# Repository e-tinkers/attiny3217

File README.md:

## E-Tinkers ATtiny3217 Arduino-Compatible Development Board

This is the hardware design repository for a tiny (34.6mm * 19.3mm) Arduino-compatible Development Board based on ATtiny3271.

ATtiny3217 is a modern AVR microcontroller chip from Microchip that could potentially replace ATmega328p that is widely used in official Arduino boards. Traditionally the classic ATtiny family has low flash and SRAM memory size as well as low pin count, this has changed since the release of tinyAVR 0-series and 1-series MCUs in 2018. The following table shows ATtiny3217 offers almost all the features of an ATmega328p and more...

### Differences between ATmega328p and ATtiny3217
<table>
    <tr>
        <th></th>
        <th>ATmega328p</th>
        <th>ATtiny3217</th>
    </tr>
    <tr>
        <td>Flash Memory</td>
        <td>32K Bytes</td>
        <td>32K Bytes</td>
    </tr>
    <tr>
        <td>SRAM</td>
        <td>2K Bytes</td>
        <td>2K Bytes</td>
    </tr>
    <tr>
        <td>EEPROM</td>
        <td>1K Bytes</td>
        <td>256 Bytes</td>
    </tr>
    <tr>
        <td>UART</td>
        <td>1</td>
        <td>1</td>
    </tr>
    <tr>
        <td>SPI</td>
        <td>1</td>
        <td>1</td>
    </tr>
    <tr>
        <td>I2C</td>
        <td>1</td>
        <td>1</td>
    </tr>
    <tr>
        <td>ADC Channel</td>
        <td>8 x 10-bit</td>
        <td>12 x 10-bit</td>
    </tr>
    <tr>
        <td>PWM Channel</td>
        <td>6</td>
        <td>8</td>
    </tr>
    <tr>
        <td>IO</td>
        <td>23</td>
        <td>22</td>
    </tr>
    <tr>
        <td rowspan="3">Timer</td>
        <td rowspan="3">
        2 x 8-bit<br>
        1 x 16-bit
        </td>
        <td rowspan="3">
        1 x 16-bit(TCA)<br>
        2 x 16-bit (TCB)<br>
        1 x 12-bit (TCD)
        </td>
    </tr>
</table>

There are several notible features that are not available in ATmega328p, such as:
<ul>
<li>Three 8-bit DACs with one external channel</li>
<li>Configurable Custom Logic/Lookup Table</li>
<li>16-bit Real-time Counter</li>
<li>6 Event System Channels</li>
<li>Periperral Touch Controller</li>
<li>5 Configurable Internal Voltage References (versus ATmega328p's 1 at VCC level)</li>
</ul>

Read my [blog](https://www.e-tinkers.com/2020/07/arduino-compatible-development-board-with-attiny3217) for more details on how to use it as an Arduino.

## E-Tinkers ATtiny3217 Development Board Pinout

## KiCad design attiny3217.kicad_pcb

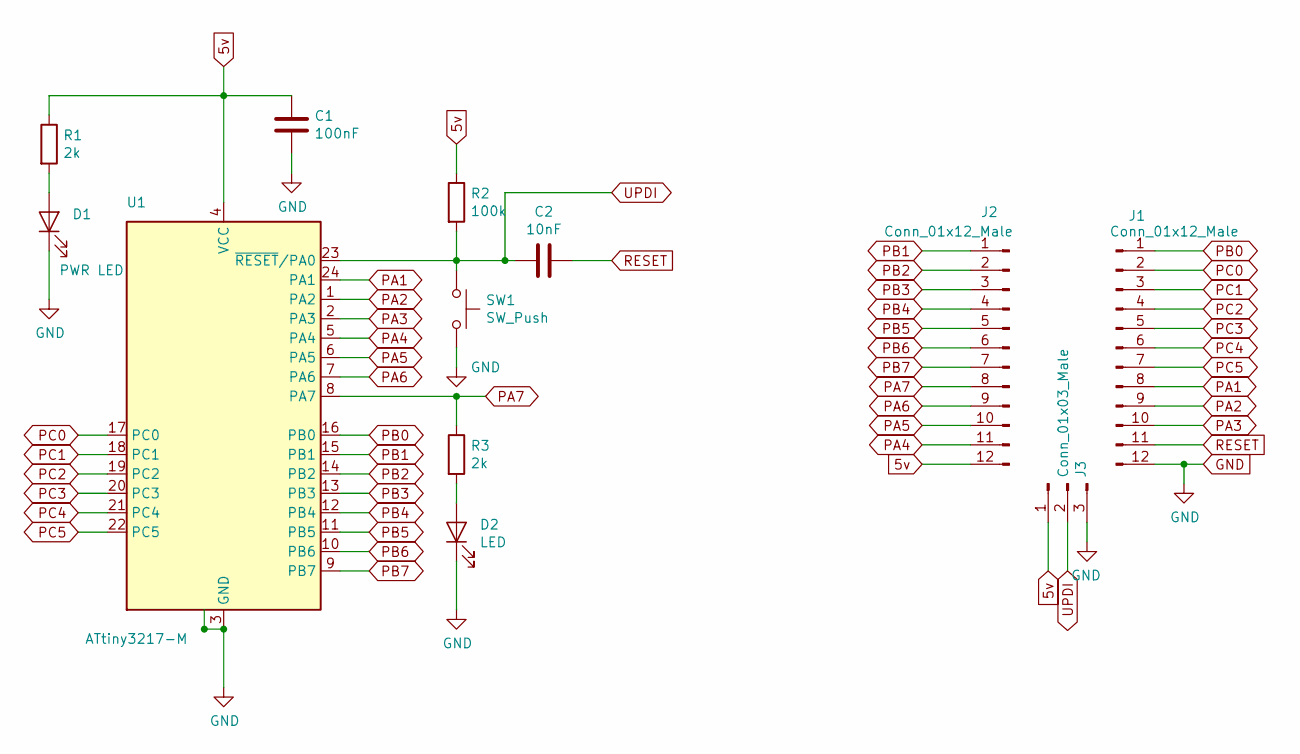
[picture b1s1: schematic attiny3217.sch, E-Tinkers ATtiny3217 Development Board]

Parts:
C1: 100nF; C_0805_2012Metric
C2: 10nF; C_0805_2012Metric
D1: PWR LED; LED_0805_2012Metric
D2: LED; LED_0805_2012Metric
J1, J2: Conn_01x12_Male; PinHeader_1x12_P2.54mm_Vertical
J3: Conn_01x03_Male; PinHeader_1x03_P2.54mm_Horizontal
R1, R3: 2k; R_0805_2012Metric
R2: 100k; R_0805_2012Metric
SW1: SW_Push; SW_SPST_CK_RS282G05A3
U1: ATtiny3217-M; QFN-24-1EP_4x4mm_P0.5mm_EP2.6x2.6mm

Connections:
5v: C1.1, J2.12, J3.1, R1.1, R2.1, U1.4 (VCC)
GND: C1.2, D1.1 (K), D2.1 (K), J1.12, J3.3, SW1.2, U1.3 (GND), U1.25 (GND)
unnamed: D1.2 (A), R1.2
unnamed: D2.2 (A), R3.2
PA1: J1.8, U1.24 (PA1)
PA2: J1.9, U1.1 (PA2)
PA3: J1.10, U1.2 (PA3)
PA4: J2.11, U1.5 (PA4)
PA5: J2.10, U1.6 (PA5)
PA6: J2.9, U1.7 (PA6)
PA7: J2.8, R3.1, U1.8 (PA7)
PB0: J1.1, U1.16 (PB0)
PB1: J2.1, U1.15 (PB1)
PB2: J2.2, U1.14 (PB2)
PB3: J2.3, U1.13 (PB3)
PB4: J2.4, U1.12 (PB4)
PB5: J2.5, U1.11 (PB5)
PB6: J2.6, U1.10 (PB6)
PB7: J2.7, U1.9 (PB7)
PC0: J1.2, U1.17 (PC0)
PC1: J1.3, U1.18 (PC1)
PC2: J1.4, U1.19 (PC2)
PC3: J1.5, U1.20 (PC3)
PC4: J1.6, U1.21 (PC4)
PC5: J1.7, U1.22 (PC5)
RESET: C2.1, J1.11
UPDI: C2.2, J3.2, R2.2, SW1.1, U1.23 (~RESET~/PA0)

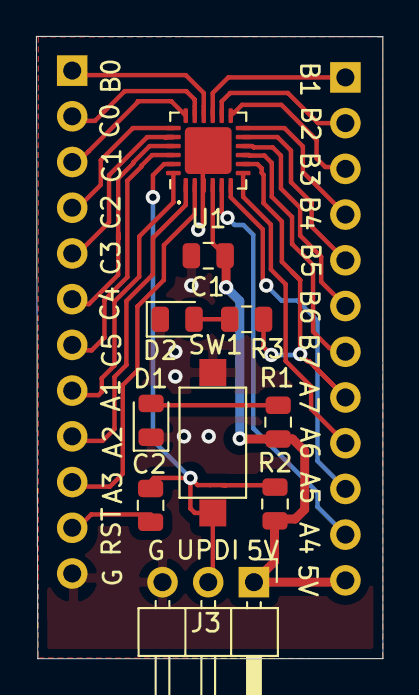
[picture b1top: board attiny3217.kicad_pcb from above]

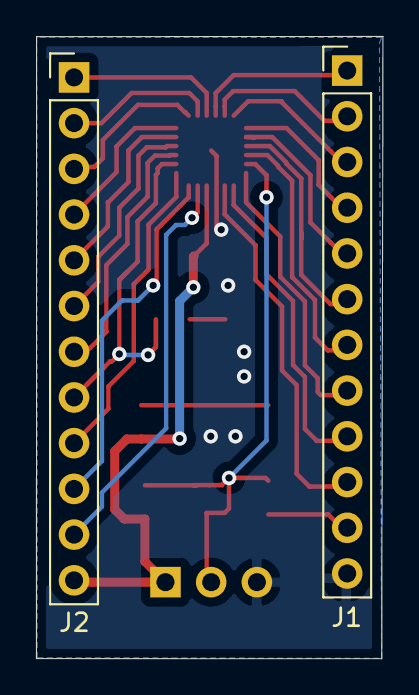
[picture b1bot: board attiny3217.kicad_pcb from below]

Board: 2 copper layers, 19.3 x 34.6 mm, 12 parts (2 on the bottom side), 27 nets.

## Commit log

2020-07-28 correct image URL
2020-07-28 remove blockquote from README
2020-07-28 shorten README
2020-07-28 shorten comparison table on README
2020-08-10 correct some misleading info on README
2020-08-10 minor correction on README
2020-11-20 add pinout diagram
2020-11-20 reduce image size
2022-01-18 remove pdf file
2022-01-18 consolidate files from two directories
